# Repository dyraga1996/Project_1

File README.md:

# Project_1
Wandering point - schema and PCB made in Eagle. Five LEDs that turn on and off one after the other.

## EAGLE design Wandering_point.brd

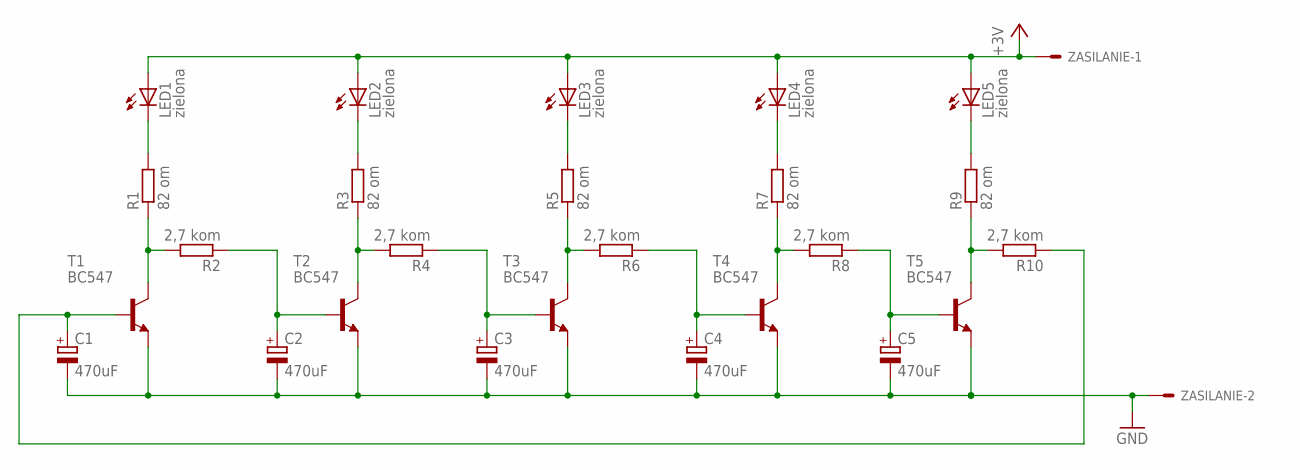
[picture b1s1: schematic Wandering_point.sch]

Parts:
C1, C2, C3, C4, C5: 470uF; E7,5-16
LED1, LED2, LED3, LED4, LED5: zielona; LED5MM
R1, R3, R5, R7, R9: 82 om; VMTA55
R2, R4, R6, R8, R10: 2,7 kom; VMTA55
T1, T2, T3, T4, T5: BC547; TO92
ZASILANIE: 332-02

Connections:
+3V3: LED1.A, LED2.A, LED3.A, LED4.A, LED5.A, ZASILANIE.1
GND: C1.-, C2.-, C3.-, C4.-, C5.-, T1.1 (E), T2.1 (E), T3.1 (E), T4.1 (E), T5.1 (E), ZASILANIE.2
unnamed: R1.1, R2.2, T1.3 (C)
unnamed: LED1.K (C), R1.2
unnamed: R3.1, R4.2, T2.3 (C)
unnamed: LED2.K (C), R3.2
unnamed: C2.+, R2.1, T2.2 (B)
unnamed: R5.1, R6.2, T3.3 (C)
unnamed: C3.+, R4.1, T3.2 (B)
unnamed: LED3.K (C), R5.2
unnamed: R7.1, R8.2, T4.3 (C)
unnamed: LED4.K (C), R7.2
unnamed: C4.+, R6.1, T4.2 (B)
unnamed: R9.1, R10.2, T5.3 (C)
unnamed: LED5.K (C), R9.2
unnamed: C5.+, R8.1, T5.2 (B)
unnamed: C1.+, R10.1, T1.2 (B)

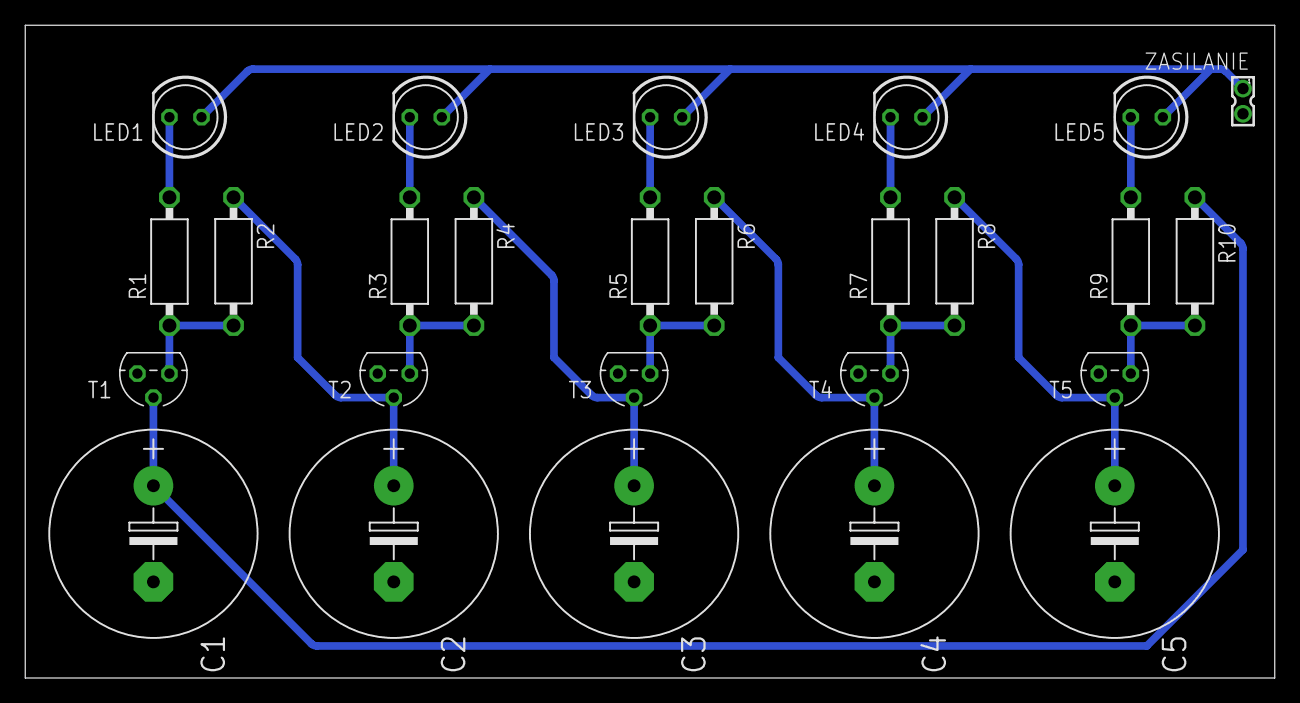
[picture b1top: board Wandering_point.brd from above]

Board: 2 copper layers, 99.0 x 51.7 mm, 26 parts (0 on the bottom side), 17 nets.

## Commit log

2020-02-02 Add schema
2020-02-02 Add PCB project
2020-02-10 Add README file
